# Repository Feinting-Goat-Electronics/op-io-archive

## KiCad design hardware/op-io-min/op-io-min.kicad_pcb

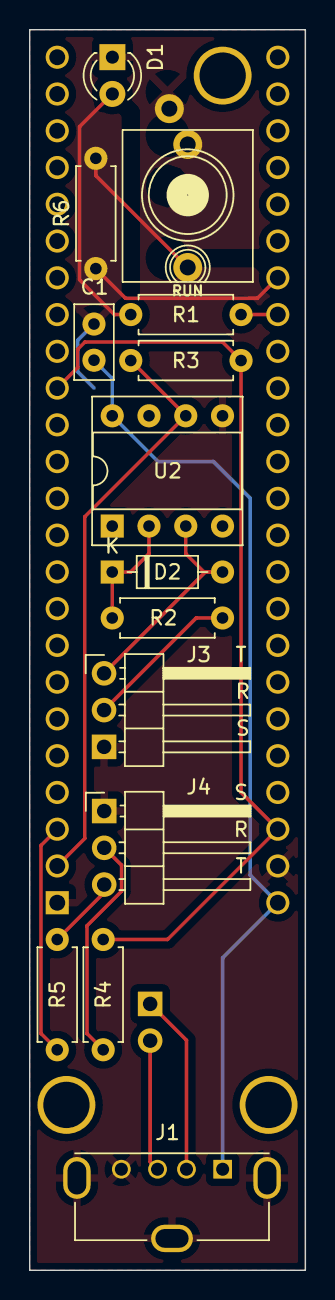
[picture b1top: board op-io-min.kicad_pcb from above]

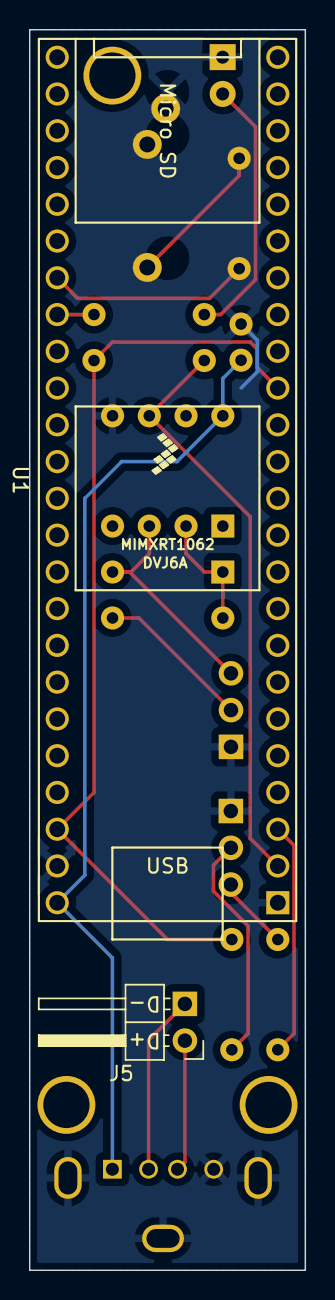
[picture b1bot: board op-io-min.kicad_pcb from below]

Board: 2 copper layers, 19.0 x 85.7 mm, 19 parts (2 on the bottom side), 16 nets.

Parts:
C1: 0.1uF; C_Disc_D5.0mm_W2.5mm_P2.50mm
D1: LED; LED_D3.0mm
D2: 1N4148; D_DO-35_SOD27_P7.62mm_Horizontal
H1, H1#2, H1#3: M3; MountingHole_M3_Skinny
J1: USB_A; USB_A_Molex_105057_Vertical
J2: RUN; AudioJack_WQP518MA
J3: MIDI_IN; PinHeader_1x03_P2.54mm_Horizontal
J4: MIDI_OUT; PinHeader_1x03_P2.54mm_Horizontal
J5: USB_HEADER; PinHeader_1x02_P2.54mm_Horizontal
R1, R2: 220; R_Axial_DIN0207_L6.3mm_D2.5mm_P7.62mm_Horizontal
R3: 470; R_Axial_DIN0207_L6.3mm_D2.5mm_P7.62mm_Horizontal
R4, R5: 47; R_Axial_DIN0207_L6.3mm_D2.5mm_P7.62mm_Horizontal
R6: 1K; R_Axial_DIN0207_L6.3mm_D2.5mm_P7.62mm_Horizontal
U1: Teensy4.1; Teensy41
U2: 6N138; DIP-8_W7.62mm_Socket

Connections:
+3.3V: R3.1, R4.2, U1.15 (3V3), U1.46 (3V3)
+5V: C1.1, J1.1 (VBUS), U1.48 (VIN), U2.8 (VCC)
GND: C1.2, D1.1 (K), J1.4 (GND), J1.5 (Shield), J2.S (Sleeve), J3.1, J4.1, U1.1 (GND), U1.47 (GND), U2.5 (GND)
LED: R1.1, U1.32 (40_A16)
unnamed: D1.2 (A), R1.2
unnamed: D2.2 (A), J3.3, U2.3 (C2)
unnamed: D2.1 (K), R2.2, U2.2 (C1)
unnamed: J1.3 (D+), J5.2
unnamed: J1.2 (D-), J5.1
unnamed: J2.T (Tip), R6.2
unnamed: J3.2, R2.1
unnamed: J4.2, R4.1
unnamed: J4.3, R5.1
RUN: R6.1, U1.31 (39_MISO1_OUT1A)
SERIAL_RECEIVE: R3.2, U1.2 (0_RX1_CRX2_CS1), U2.6 (VO2)
SERIAL_TRANSMIT: R5.2, U1.3 (1_TX1_CTX2_MISO1)

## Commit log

2023-06-04 added arduino sketch
2023-06-04 added commented stuff back
2023-06-04 added KiCad stuff
2023-06-04 cleaning
2023-06-04 added output impedance resistor
2023-10-03 init
